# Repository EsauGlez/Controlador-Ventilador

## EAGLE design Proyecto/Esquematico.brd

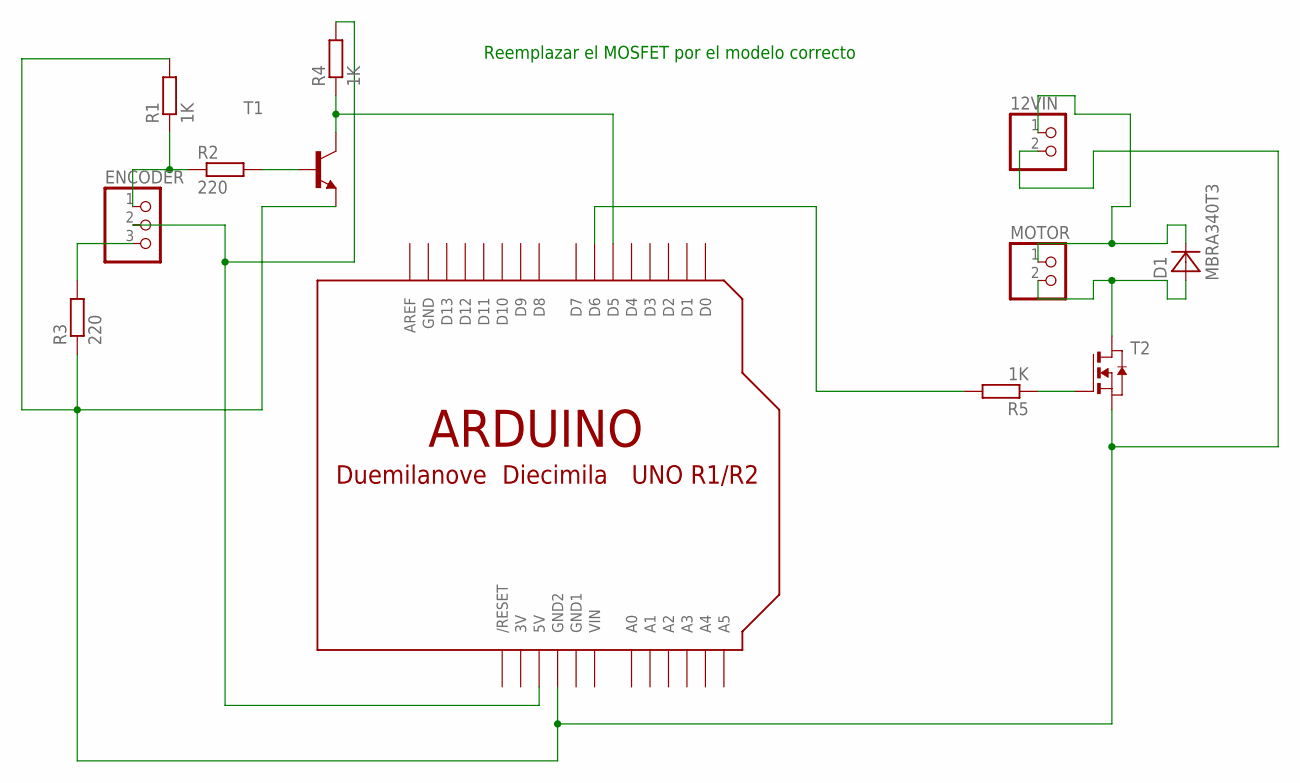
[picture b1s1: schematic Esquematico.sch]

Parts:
12VIN: PINHD-1X2; 1X02
D1: MBRA340T3; SMA
ENCODER: PINHD-1X3CB; 1X03-CLEANBIG
MOTOR: PINHD-1X2; 1X02
R1, R4, R5: 1K; R1206
R2, R3: 220; R1206
T1: BC817-40LT1-NPN-SOT23-BEC; SOT23-BEC
T2: NMOSSOT223; SOT223
U$1: ARDUINO-NOHOLE

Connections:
3V: U$1.3V
GND: U$1.GND
GND1: U$1.GND1
unnamed: ENCODER.3, R3.2
unnamed: 12VIN.2, R1.2, R3.1, T1.E, T2.3 (S), U$1.GND2
unnamed: ENCODER.2, R4.2, U$1.5V
unnamed: ENCODER.1, R1.1, R2.1
unnamed: R5.1, T2.1 (G)
unnamed: R2.2, T1.B
unnamed: D1.A, MOTOR.2, T2.2 (D), T2.4 (D)
unnamed: 12VIN.1, D1.C, MOTOR.1
unnamed: R5.2, U$1.D6
unnamed: R4.1, T1.C, U$1.D5
VIN: U$1.VIN

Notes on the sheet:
Reemplazar el MOSFET por el modelo correcto

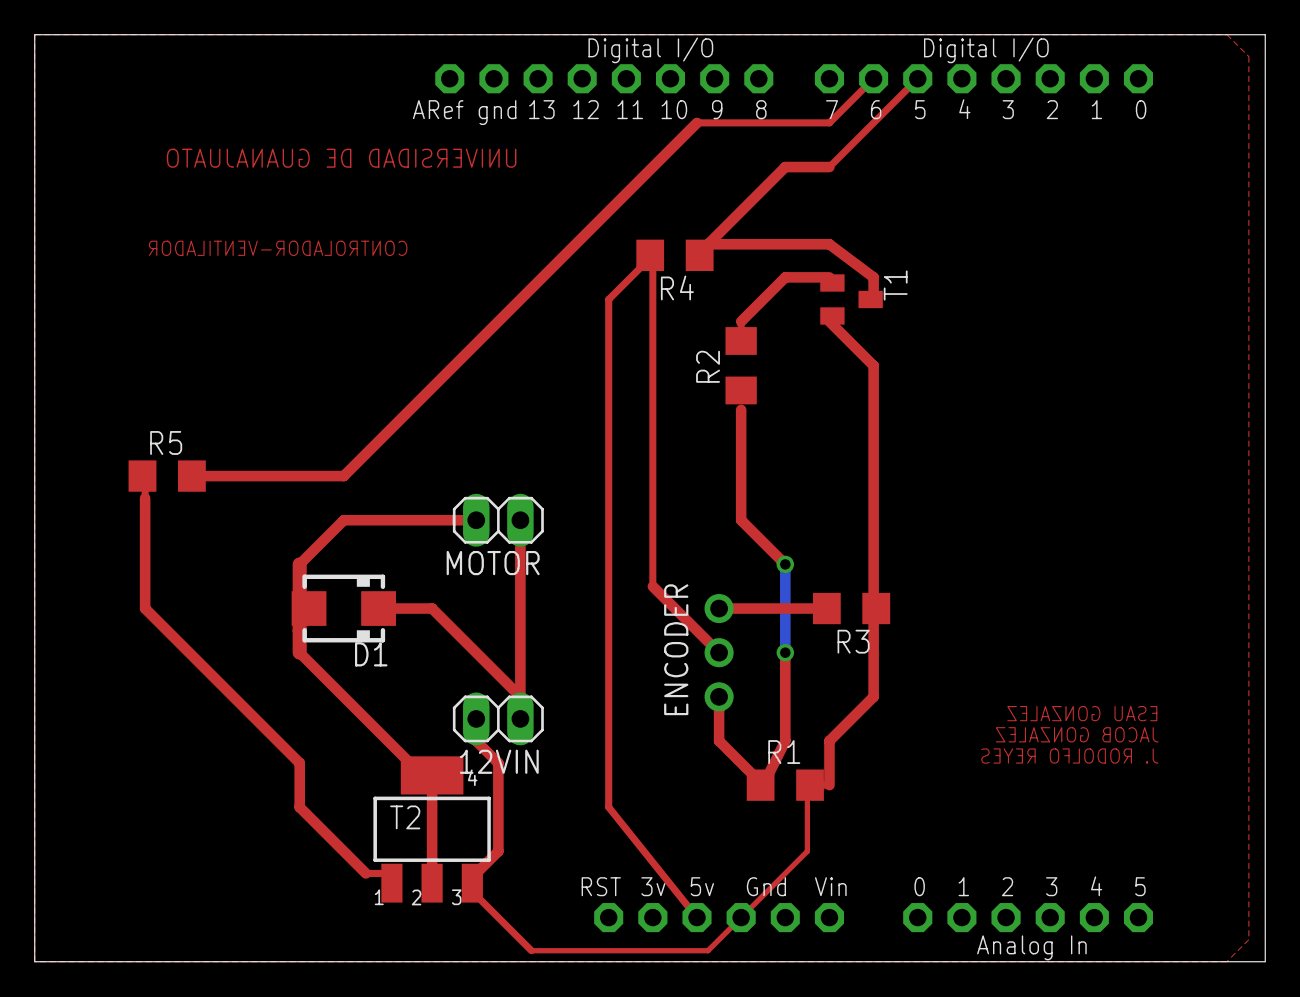
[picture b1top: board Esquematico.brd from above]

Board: 2 copper layers, 70.8 x 53.3 mm, 12 parts (0 on the bottom side), 10 nets.

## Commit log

2014-10-31 Codigo en Arduino
2014-11-20 Tarjeta PCB
2014-11-25 Se corrigieron algunas pistas
2014-12-03 Programas Arduino-Matlab para control
2014-12-03 Mejora en codigo arduino del controlador -identar-
